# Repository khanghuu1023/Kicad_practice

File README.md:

# Kicad_practice
a place for all my Kicad practice

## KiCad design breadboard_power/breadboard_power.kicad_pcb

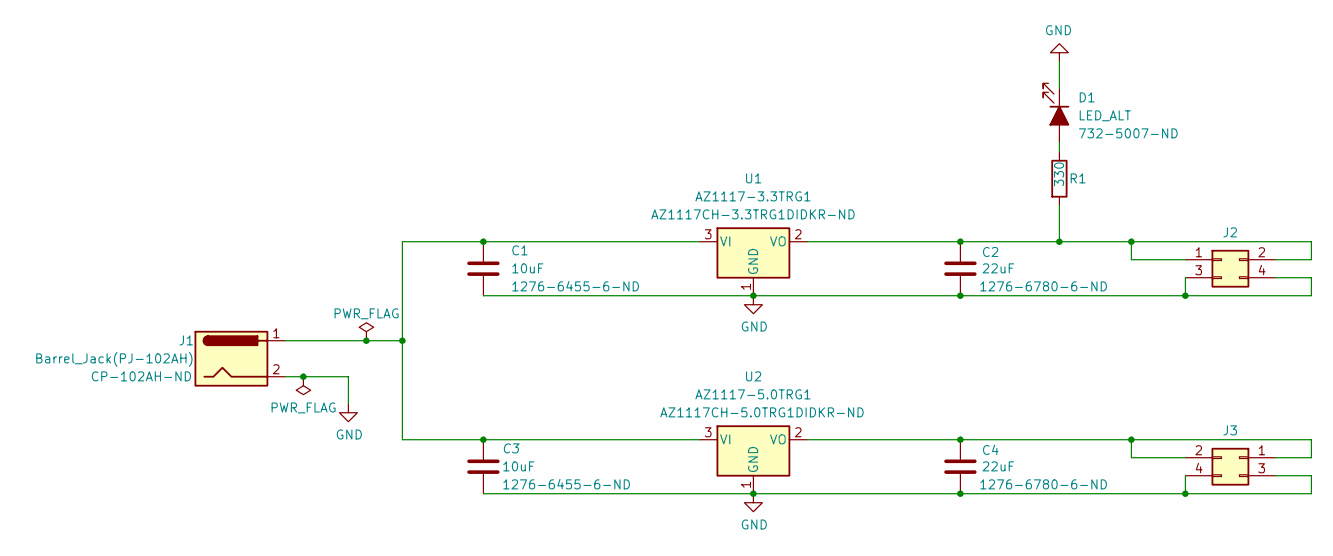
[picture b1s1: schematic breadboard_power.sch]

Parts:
C1, C3: 10uF; C_0805_2012Metric_Pad1.18x1.45mm_HandSolder; DIGIKEY 1276-6455-6-ND
C2, C4: 22uF; C_0805_2012Metric_Pad1.18x1.45mm_HandSolder; DIGIKEY 1276-6780-6-ND
D1: LED_ALT; LED_D3.0mm; DIGIKEY 732-5007-ND
J1: Barrel_Jack(PJ-102AH); BarrelJack_CUI_PJ-102AH_Horizontal; DIGIKEY CP-102AH-ND
J2, J3: Conn_02x02_Odd_Even; PinHeader_2x02_P2.54mm_Vertical
R1: 330; R_0805_2012Metric_Pad1.20x1.40mm_HandSolder
U1: AZ1117-3.3TRG1; SOT-223-3_TabPin2; DIGIKEY AZ1117CH-3.3TRG1DIDKR-ND
U2: AZ1117-5.0TRG1; SOT-223-3_TabPin2; DIGIKEY AZ1117CH-5.0TRG1DIDKR-ND

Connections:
GND: C1.2, C2.2, C3.2, C4.2, D1.1 (K), J1.2, J2.3, J2.4, J3.3, J3.4, U1.1 (GND), U2.1 (GND)
unnamed: C1.1, C3.1, J1.1, U1.3 (VI), U2.3 (VI)
unnamed: C2.1, J2.1, J2.2, R1.2, U1.2 (VO)
unnamed: C4.1, J3.1, J3.2, U2.2 (VO)
unnamed: D1.2 (A), R1.1

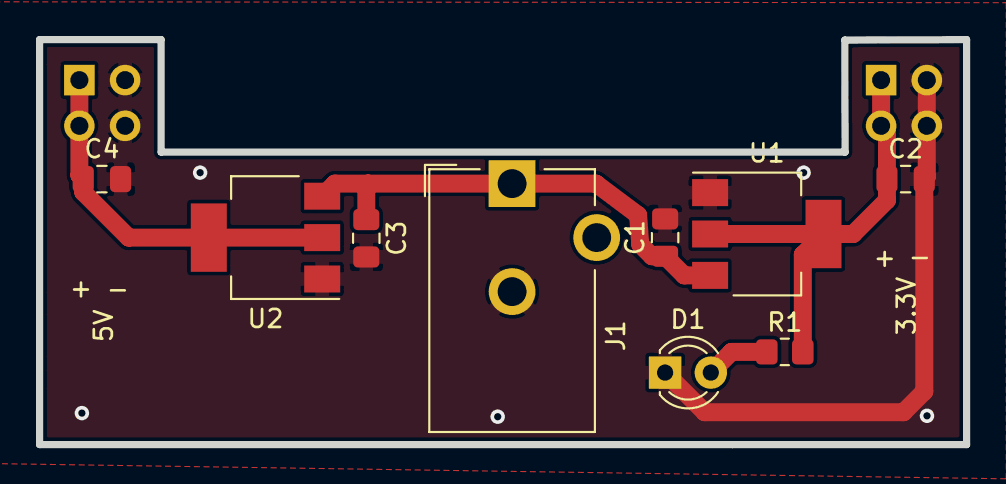
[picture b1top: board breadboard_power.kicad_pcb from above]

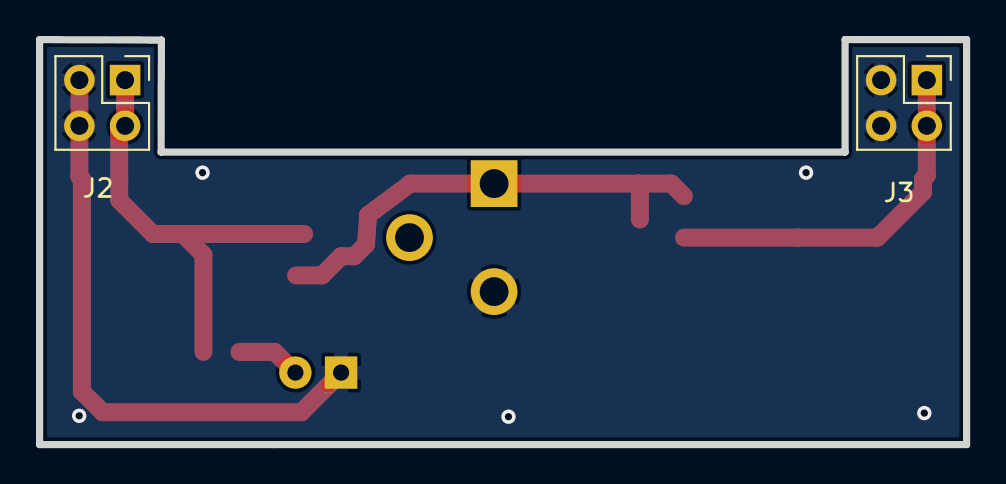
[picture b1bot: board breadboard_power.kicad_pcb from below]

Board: 2 copper layers, 51.5 x 22.5 mm, 11 parts (2 on the bottom side), 5 nets.

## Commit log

2021-06-03 Create abc
2021-06-03 Create cdf
2021-06-03 Create breadboard_power
2021-06-04 Create file
